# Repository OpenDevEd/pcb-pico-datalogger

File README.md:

Pico Datalogger with Integrated Power-Management
================================================

This is a breakout supporting low-frequency data-logging with a Raspberry Pi Pico.

Core functions:
  * log data to a micro-sd card
  * software-controlled power-control with very low standby current

From a technical viewpoint the breakout allows you to
  * turn on the system using a button or
  * use a RTC-alarm to trigger wakup
  * turn off the system using a dedicated digital-io
  * power the system from a lipo or battery-pack
  * keep time using a coincell backup-battery even if the board is not powered

Hardware Components
-------------------

Time-keeping uses the PCF8523 RTC with its integrated suport for a backup-battery.

Powermanagement uses a D-type flip-flop which drives the enable pin of the Pico.
In "reset"-state, the enable pin is pulled high and the Pico is running. The
reset is triggered either by a button, or by an RTC-alarm.

The "done"-pin of the Pico is connected to the CLK-pin of the flip-flop. A rising edge
will toggle the enable pin.

A micro-sd card reader is connected to SPI to enable logging of data.

Various additional connectors allow the user to connect sensors or displays.

License
-------

[![CC BY-SA 4.0][cc-by-sa-shield]][cc-by-sa]

This work is licensed under a
[Creative Commons Attribution-ShareAlike 4.0 International
License][cc-by-sa].

[![CC BY-SA 4.0][cc-by-sa-image]][cc-by-sa]

[cc-by-sa]: http://creativecommons.org/licenses/by-sa/4.0/
[cc-by-sa-image]: https://licensebuttons.net/l/by-sa/4.0/88x31.png
[cc-by-sa-shield]:
https://img.shields.io/badge/License-CC%20BY--SA%204.0-lightgrey.svg

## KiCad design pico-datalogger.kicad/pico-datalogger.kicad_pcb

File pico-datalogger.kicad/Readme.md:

KiCAD-Designfiles
=================

Here are the KiCAD (v6) design-files for the Datalogger-PCB.

Schematic
---------

Layout
------

3D-Views
--------

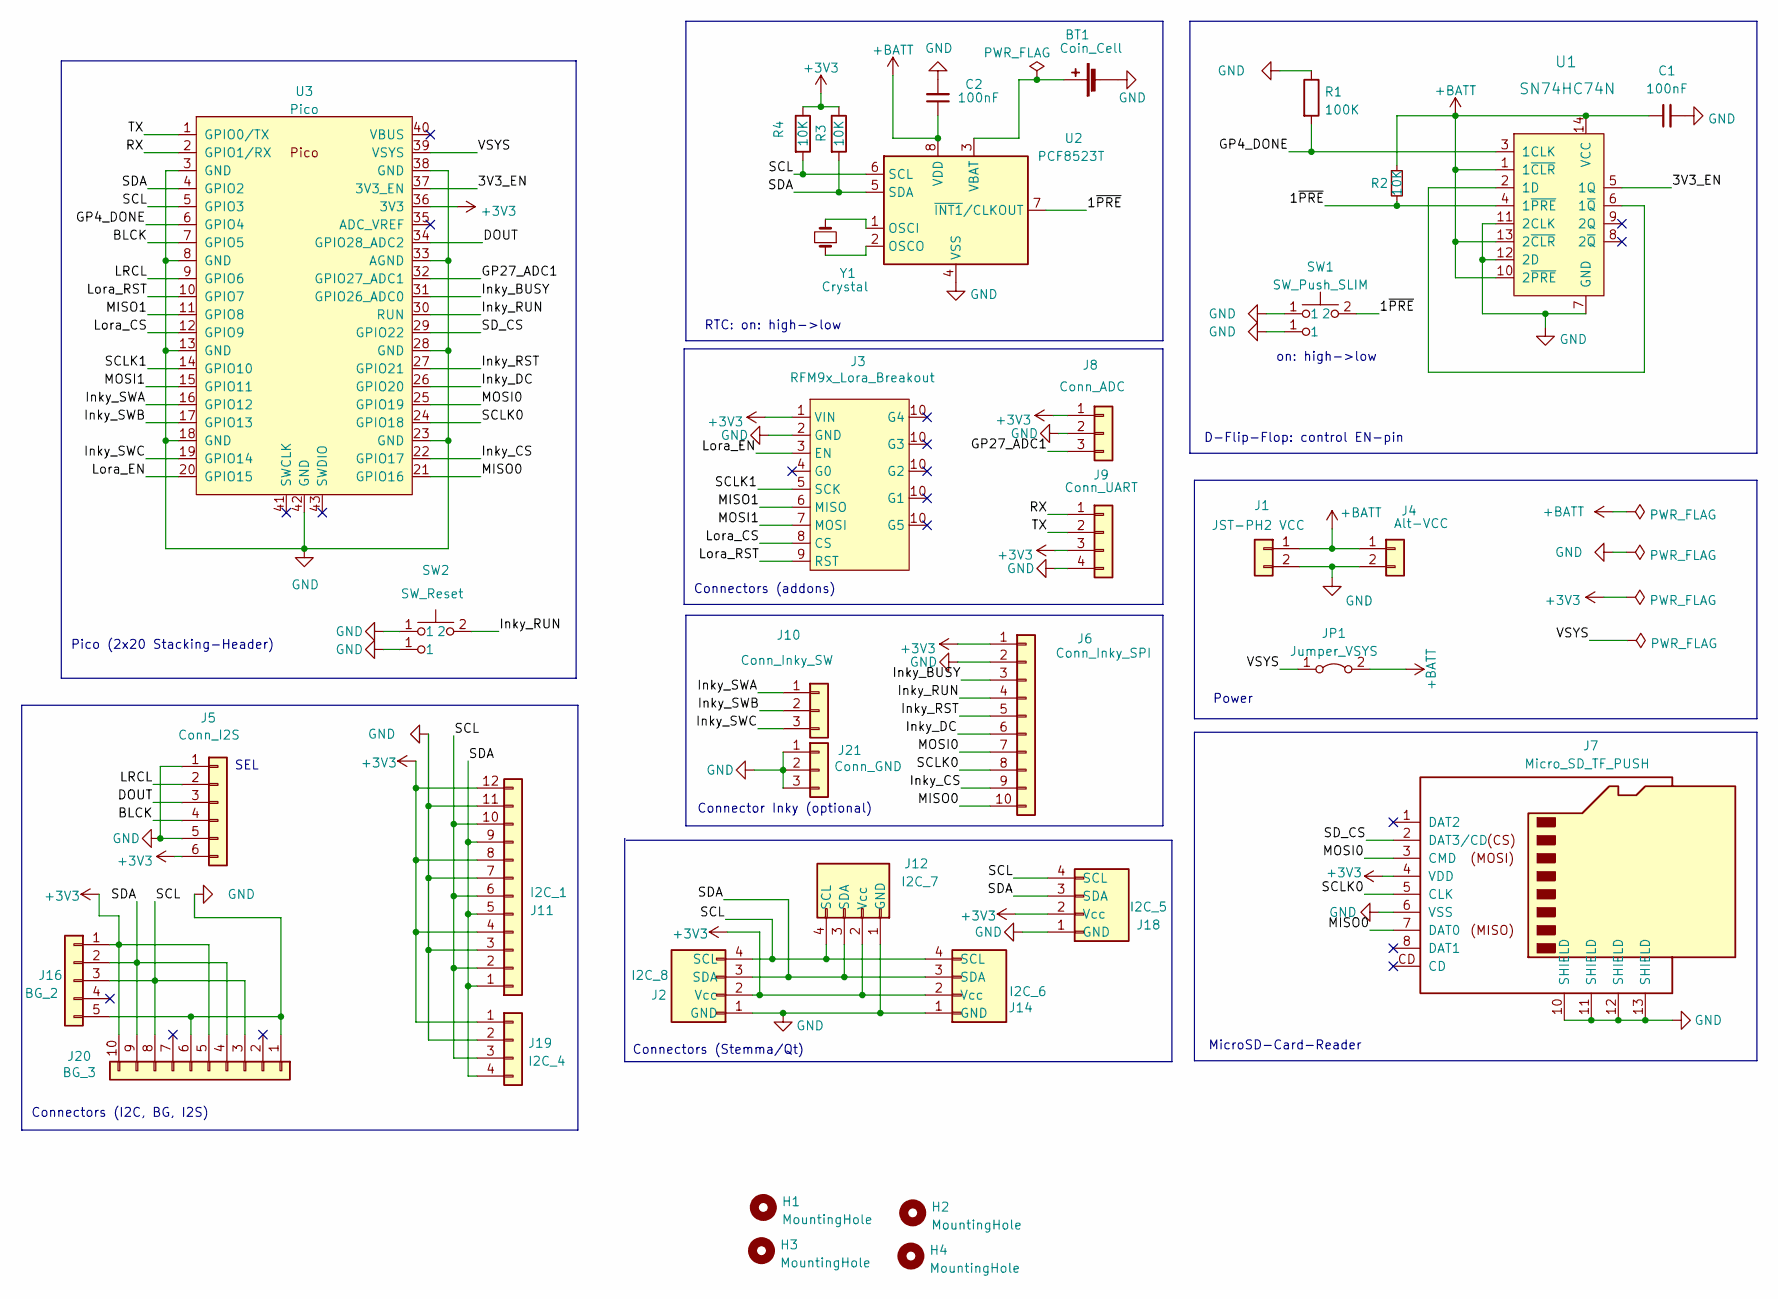
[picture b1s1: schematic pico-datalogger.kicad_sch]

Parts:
BT1: Coin_Cell; CR2032_Holder; LCSC C964777
C1, C2: 100nF; C_0402_1005Metric; LCSC C1525
H1, H2, H3, H4: MountingHole; MountingHole_2.5mm
J1: JST-PH2 VCC; JST_PH_S2B-PH-SM4-TB_1x02-1MP_P2.00mm_Horizontal
J2: I2C_8; JST_SH_SM04B-SRSS-TB_1x04-1MP_P1.00mm_Horizontal
J3: RFM9x_Lora_Breakout
J4: Alt-VCC; PinHeader_1x02_P2.54mm_Vertical
J5: Conn_I2S; PinHeader_1x06_P2.54mm_Vertical
J6: Conn_Inky_SPI; PinHeader_1x10_P2.54mm_Vertical
J7: Micro_SD_TF_PUSH; TF-Push; LCSC C393941
J8: Conn_ADC; PinHeader_1x03_P2.54mm_Horizontal
J9: Conn_UART; PinHeader_1x04_P2.54mm_Horizontal
J10: Conn_Inky_SW; PinHeader_1x03_P2.54mm_Vertical
J11: I2C_1; PinHeader_1x12_P2.54mm_Horizontal
J12: I2C_7; JST_SH_SM04B-SRSS-TB_1x04-1MP_P1.00mm_Horizontal
J14: I2C_6; JST_SH_SM04B-SRSS-TB_1x04-1MP_P1.00mm_Horizontal
J16: BG_2; PinHeader_1x05_P2.54mm_Vertical
J18: I2C_5; JST_SH_BM04B-SRSS-TB_1x04-1MP_P1.00mm_Vertical
J19: I2C_4; PinHeader_1x04_P2.54mm_Vertical
J20: BG_3; PinHeader_1x10_P2.54mm_Horizontal
J21: Conn_GND; PinHeader_1x03_P2.54mm_Vertical
JP1: Jumper_VSYS; PinHeader_1x02_P2.54mm_Vertical
R1: 100K; R_0402_1005Metric; LCSC C25741
R2, R3, R4: 10K; R_0402_1005Metric; LCSC C25744
SW1: SW_Push_SLIM; SW_PUSH_SLIM_1x4
SW2: SW_Reset; SW_PUSH_SLIM_1x4
U1: SN74HC74N; SOIC-14_3.9x8.7mm_P1.27mm; MPN SN74HC74N; Digi-Key_PN 296-1602-5-ND
U2: PCF8523T; SOIC-8_3.9x4.9mm_P1.27mm; LCSC C2651516
U3: Pico; RPi_Pico_TH_nodbg
Y1: Crystal; Crystal_SMD_3215-2Pin_3.2x1.5mm; LCSC C32346

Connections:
+3V3: J2.2 (Vcc), J3.1 (VIN), J5.6, J6.1, J7.4 (VDD), J8.1, J9.3, J11.4, J11.8, J11.12, J12.2 (Vcc), J14.2 (Vcc), J16.1, J18.2 (Vcc), J19.1, J20.5, J20.10, R3.1, R4.1, U3.36 (3V3)
+BATT: C1.1, C2.1, J1.1, J4.1, JP1.2 (B), R2.1, U1.1 (1~CLR), U1.10 (2~PRE), U1.13 (2~CLR), U1.14 (VCC), U2.8 (VDD)
/1~PRE: R2.2, SW1.2, U1.4 (1~PRE), U2.7 (~INT1/CLKOUT)
/3V3_EN: U1.5 (1Q), U3.37 (3V3_EN)
/BLCK: J5.4, U3.7 (GPIO5)
/DOUT: J5.3, U3.34 (GPIO28_ADC2)
/GP4_DONE: R1.2, U1.3 (1CLK), U3.6 (GPIO4)
/GP27_ADC1: J8.3, U3.32 (GPIO27_ADC1)
/Inky_BUSY: J6.3, U3.31 (GPIO26_ADC0)
/Inky_CS: J6.9, U3.22 (GPIO17)
/Inky_DC: J6.6, U3.26 (GPIO20)
/Inky_RST: J6.5, U3.27 (GPIO21)
/Inky_RUN: J6.4, SW2.2, U3.30 (RUN)
/Inky_SWA: J10.1, U3.16 (GPIO12)
/Inky_SWB: J10.2, U3.17 (GPIO13)
/Inky_SWC: J10.3, U3.19 (GPIO14)
/LRCL: J5.2, U3.9 (GPIO6)
/Lora_CS: J3.8 (CS), U3.12 (GPIO9)
/Lora_EN: J3.3 (EN), U3.20 (GPIO15)
/Lora_RST: J3.9 (RST), U3.10 (GPIO7)
/MISO0: J6.10, J7.7 (DAT0), U3.21 (GPIO16)
/MISO1: J3.6 (MISO), U3.11 (GPIO8)
/MOSI0: J6.7, J7.3 (CMD), U3.25 (GPIO19)
/MOSI1: J3.7 (MOSI), U3.15 (GPIO11)
/RX: J9.1, U3.2 (GPIO1/RX)
/SCL: J2.4 (SCL), J11.2, J11.6, J11.10, J12.4 (SCL), J14.4 (SCL), J16.3, J18.4 (SCL), J19.3, J20.3, J20.8, R4.2, U2.6 (SCL), U3.5 (GPIO3)
/SCLK0: J6.8, J7.5 (CLK), U3.24 (GPIO18)
/SCLK1: J3.5 (SCK), U3.14 (GPIO10)
/SDA: J2.3 (SDA), J11.1, J11.5, J11.9, J12.3 (SDA), J14.3 (SDA), J16.2, J18.3 (SDA), J19.4, J20.4, J20.9, R3.2, U2.5 (SDA), U3.4 (GPIO2)
/SD_CS: J7.2 (DAT3/CD), U3.29 (GPIO22)
/TX: J9.2, U3.1 (GPIO0/TX)
/VSYS: JP1.1 (A), U3.39 (VSYS)
GND: BT1.2 (-), C1.2, C2.2, J1.2, J2.1 (GND), J3.2 (GND), J4.2, J5.1, J5.5, J6.2, J7.6 (VSS), J7.10 (SHIELD), J7.11 (SHIELD), J7.12 (SHIELD), J7.13 (SHIELD), J8.2, J9.4, J11.3, J11.7, J11.11, J12.1 (GND), J14.1 (GND), J16.5, J18.1 (GND), J19.2, J20.1, J20.6, J21.1, J21.2, J21.3, R1.1, SW1.1, SW2.1, U1.7 (GND), U1.11 (2CLK), U1.12 (2D), U2.4 (VSS), U3.3 (GND), U3.8 (GND), U3.13 (GND), U3.18 (GND), U3.23 (GND), U3.28 (GND), U3.33 (AGND), U3.38 (GND), U3.42 (GND)
unnamed: BT1.1 (+), U2.3 (VBAT)
unnamed: U1.2 (1D), U1.6 (1~Q)
unnamed: U2.1 (OSCI), Y1.2
unnamed: U2.2 (OSCO), Y1.1

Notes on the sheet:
Power
Connector Inky (optional)
Pico (2x20 Stacking-Header)
Connectors (Stemma/Qt)
D-Flip-Flop: control EN-pin
SEL
RTC: on: high->low
Connectors (addons)
MicroSD-Card-Reader
Connectors (I2C, BG, I2S)
on: high->low

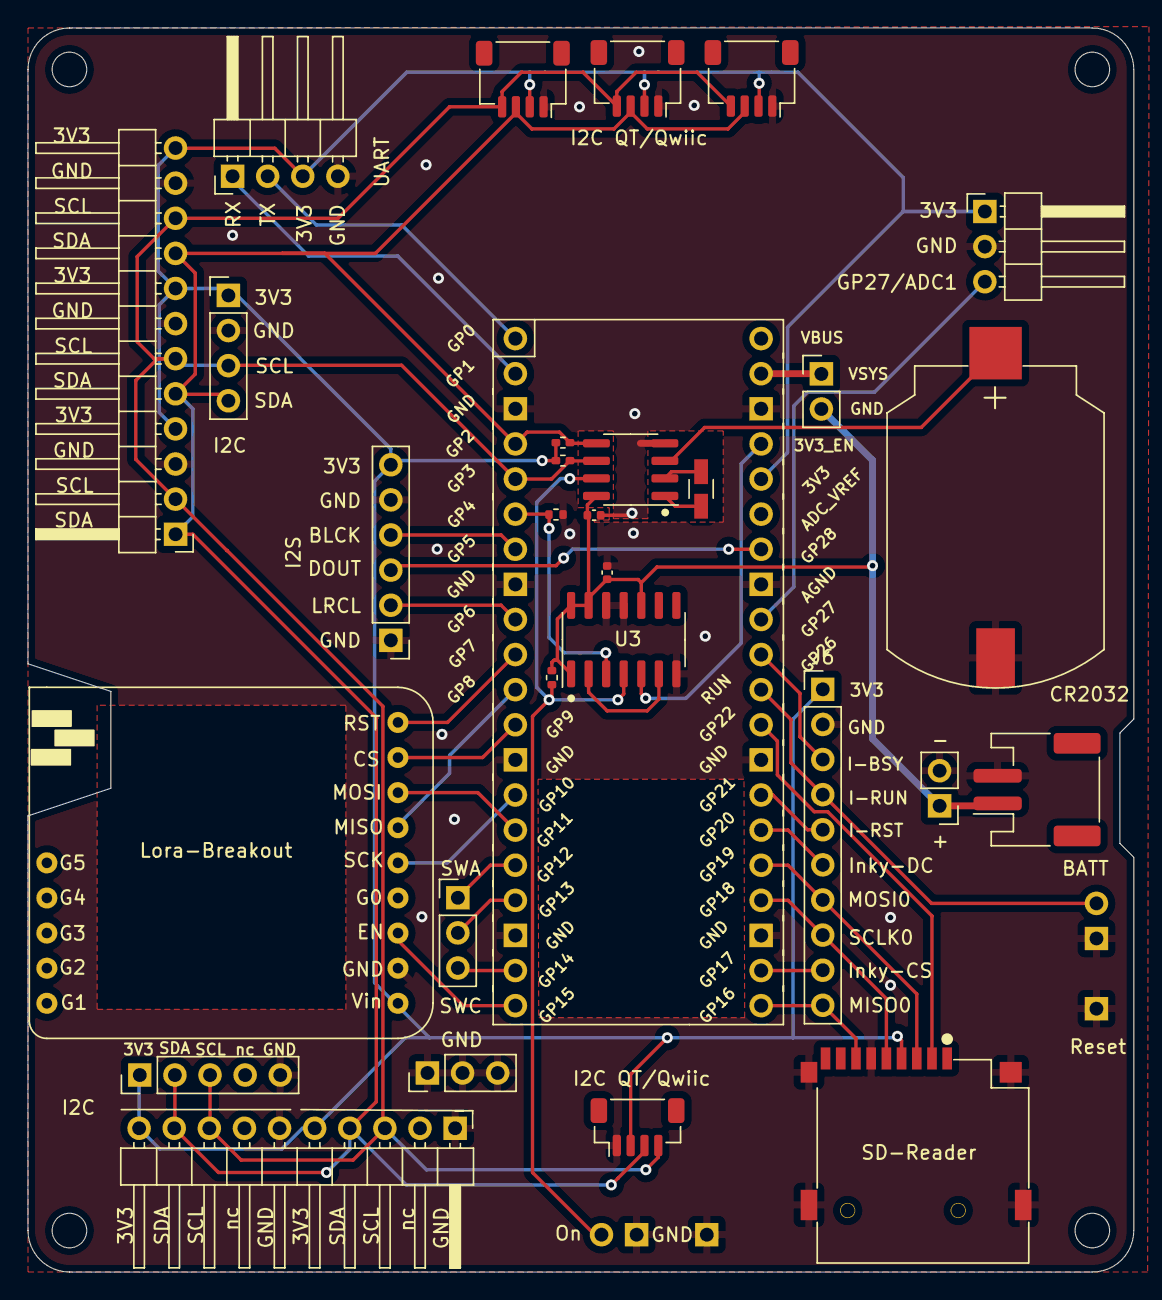
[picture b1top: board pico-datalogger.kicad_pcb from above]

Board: 2 copper layers, 80.0 x 90.0 mm, 36 parts (0 on the bottom side), 37 nets.

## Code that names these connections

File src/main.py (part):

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PIN_SCL1  = board.GP3   # connect to sensors and RTC via I2C interface

# SD-card interface (SPI)
PIN_SD_CS   = board.GP22
PIN_SD_SCK  = board.GP18
PIN_SD_MOSI = board.GP19
PIN_SD_MISO = board.GP16

# display interface (SPI, Inky-Pack) [Shares SPI with SD card]
PIN_INKY_CS   = board.GP17
PIN_INKY_RST  = board.GP21
PIN_INKY_DC   = board.GP20
PIN_INKY_BUSY = board.GP26

# Lora interface (SPI, separate)
PIN_LORA_CS   = board.GP9
PIN_LORA_RST  = board.GP7
PIN_LORA_EN  = board.GP15
PIN_LORA_SCK  = board.GP10
PIN_LORA_MOSI = board.GP11
PIN_LORA_MISO = board.GP8
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    # early setup of SD-card (in case we send debug-logs to sd-card)
    if g_config.HAVE_SD:
      self._spi = busio.SPI(PIN_SD_SCK,PIN_SD_MOSI,PIN_SD_MISO)
      self.sd_cs = DigitalInOut(PIN_SD_CS)
      sdcard     = adafruit_sdcard.SDCard(self._spi,self.sd_cs)
      self.vfs   = storage.VfsFat(sdcard)
      storage.mount(self.vfs, "/sd")
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        self.display = DisplayFactory.inky_pack(self._spi)
      elif g_config.HAVE_DISPLAY == "Ada-2.13-Mono":
        self.display = DisplayFactory.ada_2_13_mono(
          pin_dc=PIN_INKY_DC,pin_cs=PIN_INKY_CS,
          pin_rst=PIN_INKY_RST,pin_busy=PIN_INKY_BUSY,spi=self._spi)
      elif g_config.HAVE_DISPLAY == "Display-Pack":
        self.display = DisplayFactory.display_pack(self._spi)
        self.display.auto_refresh = False
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    if (g_config.HAVE_LORA):
      g_logger.print(f"we have lora")
      self._spi1 = busio.SPI(PIN_LORA_SCK,PIN_LORA_MOSI,PIN_LORA_MISO)
      CS = DigitalInOut(PIN_LORA_CS)
      RESET = DigitalInOut(PIN_LORA_RST)
      ENABLE = DigitalInOut(PIN_LORA_EN)
      ENABLE.direction  = Direction.OUTPUT
      self.lora = lora.LORA(433.0, self._spi1, CS, RESET, ENABLE)
      # payload = self.csv_header + "\n" + self.record
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g_logger.print("setup of hardware")

if g_config.LORA_RANGE_TEST:
  lora_range_test.lora_range_test(PIN_LORA_CS,PIN_LORA_RST,PIN_LORA_EN,PIN_LORA_SCK,PIN_LORA_MOSI,PIN_LORA_MISO)
else:
  app = DataCollector()
  app.setup()
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
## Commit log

2023-05-08 provide initial content
2023-05-12 intial commit
2023-05-12 updated reserved pins
2023-05-12 added battery and connectors
2023-05-12 added links to datasheets
2023-05-12 Rev. 0.8: components with footprints
2023-05-12 Rev. 0.9: initial routing
2023-05-13 add GP0/GP1 (UART) and GP27 (ADC) to reserved pins
2023-05-13 Rev. 0.95: review for production
2023-05-13 Text
2023-05-13 Test
2023-05-13 Update links.md
    Added sensor data
2023-05-13 Update README.md
    Added section on 'background'
2023-05-14 Rev 0.96: added reset-button
2023-05-14 Update pins.md
    Fixed table
2023-05-16 fix: added 3V3 and GND for InkyPack-connector
2023-05-16 added I2C/BG connectors
2023-05-19 Rev 0.98: ready for production
2023-05-23 added python-specific files
2023-05-27 Update README.md
    Added link to case
2023-06-01 re-enabled lib
2023-06-02 added LCSC-number to PCF8523T
2023-06-02 Rev 1.00: fix Stemma/Qt connectors
2023-06-05 added section 'Software'
2023-06-08 only import necessary libs
2023-06-08 added ens160 library
2023-06-08 added basic ENS160 support
2023-06-09 updated configuration-section
2023-06-09 fixes and new features (e.g. cont-mode)
2023-06-09 save_data(): print data also if we don't have a SD
2023-06-09 added hook for LORA
2023-06-09 added images of pcb
2023-06-09 added links to images
2023-06-09 Update README.md - adding hardware setup
2023-06-09 Update README.md - updated url to case
2023-06-10 added display-support
2023-06-10 fixed links
2023-06-10 shorten update-timestamp
2023-06-10 tweak labels
2023-06-11 Update main.py
    Cosmetic updates
2023-06-11 Update main.py with various switches
    Added switches (most of which not implemented)
    Changed SI for Lux to lx.
2023-06-11 Update main.py
    Added 'blink before/after' timing.
2023-06-12 minor cleanups
2023-06-12 added config.py
2023-06-12 added template for config.py
2023-06-12 read configuration from config.py
2023-06-12 documented new configuration-management
2023-06-12 add some sleep-time after display-update
2023-06-12 added pins for PDM-mic
2023-06-13 Update main.py - minor change for logging
2023-06-14 addes support for PDM micro
2023-06-14 Revert "Merge pull request #1 from bablokb/main"
2023-06-14 Manually fixing the merge - code now has PDM and latest changes from fork
2023-06-14 Fixing additional lines
2023-06-14 amend .gitignore to ignore vscode
2023-06-14 Update config_template.py
    Updated config_template with comments
2023-06-15 Update config_template.py
    Added stub for AM2301B
2023-06-15 update to newest version of dataviews-lib
2023-06-15 added adafruit_st7789
2023-06-15 start of reorg of documentation
2023-06-15 renamed layout.png -> schematic.png
2023-06-15 renamed links.md -> references.md
2023-06-15 added document linking to schematic, layout and 3D-views
2023-06-15 moved KiCAD-related images into subdir
2023-06-15 add support for display-pack
2023-06-15 fixed link to Readme in KiCAD directory
2023-06-15 fixed link to Readme in KiCAD directory (again)
2023-06-15 fixed link to Readme in KiCAD directory (3rd try)
2023-06-15 fixed links to images
2023-06-15 Adding libraries for display and bh1750
2023-06-15 Added bh1750 code
    Added code for bh1750, still need to add adafruit_bh1750.mpy to lib, see next commit
2023-06-15 Minor amend to comments
2023-06-15 Display working for sensors individually
2023-06-15 gitignore updated
2023-06-15 Display working for both sensors connected
    Added a scan.py file to scan for I2C devices connected to the microcontroller
2023-06-15 Create config_1.py
    Adding example config
2023-06-15 Reordering some functions
2023-06-15 Display edited
    Display shows data vertically
2023-06-16 updated AHT20/AM2301B
2023-06-16 code cleanup
2023-06-16 removed HAVE_AM2301B
2023-06-16 switched to DejaVuSans-16
2023-06-16 Update main.py
    Adding time to display
2023-06-17 Small fixes
2023-06-17 Update main.py
    Font: DejaVuSansMono-Bold-18-subset.bdf
2023-06-17 _create_view(): minor layout-changes
2023-06-17 Update main.py
    Added save_status to indicate issues with saving on display.
2023-06-17 Update main.py
    Added csv file header writing if file doesn't exist.
2023-06-17 Update main.py
    Tidy up sd status indicator
2023-06-18 moved FONT_INKY to FONT_DISPLAY in config-file
2023-06-18 fixed indentation errors
2023-06-18 minor fixes in csv-header
2023-06-18 raise exception of sensor-count is too high
2023-06-19 pretty print values on console
2023-06-19 save_data(): fix check for csv-file
2023-06-19 Code for SHT45
2023-06-20 implement different log-destinations
2023-06-20 CSV file with serial number | BH1745 code updated
2023-06-21 update external rtc from internal rtc
2023-06-21 global object for config-variables
2023-06-21 remove sensor-specific code
2023-06-21 Update csv
2023-06-22 dynamically configure sensors
2023-06-22 pretty_print(): minor layout fix
2023-06-22 removed pdm related code
2023-06-22 refactored sensor-code
2023-06-22 updated configuration-scheme
2023-06-23 renamed components.md -> sensors.md
2023-06-23 cleanup: removed power/components sections
2023-06-23 content moved from sensors.md
2023-06-23 document power-measurements
2023-06-23 updated links, including power
2023-06-23 updated data of BH1750 and LTR559
2023-06-23 added info about I2C0
2023-06-23 replace i2c with i2c1
2023-06-23 added support for I2C0
2023-06-24 fixed power-calculation
2023-06-24 implement CSV_FILENAME as configuration-option
2023-06-25 Update power.md - added spaces around * to avoid markdown
2023-06-25 Update bh1750.py
    This shoudl be i2c0, right?
2023-06-26 fixed i2c-bus for i2c0
2023-06-26 documented entering admin-mode
2023-06-26 implemented stub for admin-mode
2023-06-26 update main.py
    Change PDM DAT pin to GP1
    Update serials display on logger
2023-06-28 updated with new insights
2023-06-28 log detection of sensor
2023-06-29 write detected sensors into log
2023-07-02 add support for Adafruit 2.13 monochrome e-ink
2023-07-02 implement alarm from time-table
2023-07-02 Testing Display with the main branch
2023-07-03 added section about longterm test results
2023-07-04 fixed calculation of now_day and added logging
2023-07-04 fixed description of sample table
2023-07-06 Remove .DS_Store from everywhere
2023-07-06 Ignore .DS_Store files
2023-07-10 bugfix: set alarm-schedule to 'monthly'
2023-07-12 sht31 sensor
    Code and Library
2023-07-13 Update
    Few changes
2023-07-14 Fixing code for sht31
2023-07-14 Adding config and code for sensors serial numbers
    If WRITE_SERIALS is true, a table will be created with sensors name and serial number and a csv file will be written.
    Not al the sensors have a serial number attribute.
    sht31d for example has the attribute but not aht20
2023-07-14 display updated and tested
    adding a smaller font
    data panel updated more lines and less columns
2023-07-16 Added lora
2023-07-28 Updates lora.py to include range test
2023-07-28 add sendAndWaitForRespond function
